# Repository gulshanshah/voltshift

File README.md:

# VoltShift

**Automatic voltage-stable line switcher.**

In many villages and homes the supply arrives unbalanced — some lines sit weak,
some sit high, and people walk over to the board and move the home supply to the
line that behaves. VoltShift does that switching automatically: it watches three
incoming lines, picks the one that is stable near 240 V, and drives a selector
switch onto it with a stepper motor — or to OFF when no line is safe.

## Repository layout

| Path | What it is |
| --- | --- |
| `pcb/` | KiCad 9 project — `voltshift.kicad_pro`, schematic, board and netlist |
| `firmware/` | ATmega328P firmware (bare-metal C, PlatformIO) |
| `media/` | Board renders, layer plots, schematic SVG and PDF |
| `docs/` | Schematic PDF and the ERC report |

## How it works

1. **Sensing** — three identical channels (R, Y, B), each a fusible 4R7 input
   resistor, three 150k 1 % series resistors stepping the AC line down, and a
   1N4007 rectifier turning it into a DC level the MCU can read. A 4k7 shunt,
   a 5.6 V zener and a 47 µF cap clamp and smooth that level.
2. **Isolation** — each channel feeds a PC817 optocoupler, so the mains domain
   stays galvanically separate from the logic domain; the opto output lands on
   an ATmega328P ADC input through a 10k pull-down.
3. **Decision** — the MCU samples all three inputs continuously, accepts only a
   line that reads stable near 240 V, and rejects anything too high or too low.
4. **Switching** — a 28BYJ-48 stepper driven by a ULN2003A turns the selector
   through four 45° positions: the healthy line, or OFF when nothing is in
   range.

The board keeps manual switching out of the equation — the home supply always
lands on the healthiest voltage.

## Hardware

- **MCU** — ATmega328P-PU @ 16 MHz, with ISP (2×3) and 5 V TTL UART headers
- **Drive** — ULN2003A → 28BYJ-48 stepper selector
- **Sensing** — 3× opto-isolated AC channels → ADC0/1/2
- **Power** — external 5 V DC input, ferrite-isolated AVCC
- **Board** — 170 × 100 mm, 2-layer, mains domain and logic domain split with
  ≥ 6 mm creepage between them and a ground pour kept to the logic side only
- **Status** — schematic and routed PCB complete, ERC clean (0 errors,
  0 warnings)

### Safety

This board handles **240 VAC mains**. Sense resistors must be rated for the
working voltage, creepage/clearance must be respected, and the board must not
be touched while powered. It is a prototype — validate it against your local
electrical rules before putting it anywhere near a real installation.

## Media

| Top | Bottom |
| --- | --- |
|  |  |

- [Schematic (SVG)](media/voltshift.svg) · [Schematic (PDF)](media/voltshift-schematic.pdf)
- [Top copper layout](media/voltshift-layout-top.svg) · [Bottom copper layout](media/voltshift-layout-bottom.svg)

## Firmware

The firmware lives in `firmware/` and runs directly on the ATmega328P — no Arduino framework, no communication, fully automatic, about 1.8 KB of flash.

```
firmware/include/config.h   # thresholds, calibration, pin map, timing
firmware/src/adc.c           # averaged ADC reads + counts-to-decivolts calibration
firmware/src/selector.c      # line validity, best-line choice, hysteresis
firmware/src/stepper.c       # half-step driver for the 28BYJ-48 selector
firmware/src/led.c           # status LED patterns
firmware/src/main.c          # 1 ms tick, sample/evaluate loop, watchdog
```

Every 10 ms each channel is averaged and converted to decivolts; every 100 ms a line is accepted only if it sits inside 205.0–255.0 V with under 2.0 V of ripple. The selector moves to the accepted line closest to 240 V, only after that line beats the held one by more than 3 V for four consecutive evaluations, and drops to OFF the moment the held line goes invalid. The status LED reports state: slow blink while starting up, solid on a line, fast blink on OFF or while the motor is moving.

Build and flash with PlatformIO:

```
cd firmware
pio run                     # builds firmware.elf / firmware.hex
pio run -t upload           # default programmer is usbasp (ISP)
```

Calibration is per-channel in `include/config.h` — `VS_CAL_OFFSET_*` and `VS_CAL_SPAN_*_PER_100V` map raw ADC counts to voltage; tune them against a known-good meter before trusting the decisions.

## Working on the design

Open `pcb/voltshift.kicad_pro` in KiCad 9 and edit the schematic and the board
directly. Run the Electrical Rules Checker after any change — the last check
came back clean (0 errors, 0 warnings).

Keep the two domains apart while editing: mains circuitry stays left of the
isolation gap, the ground pour belongs to the logic side only, and the 6 mm
creepage between them must survive any move. The exported schematic PDF and
the ERC report are in `docs/`.

## Status

Schematic and PCB are done and ERC-clean, and the firmware builds for the
ATmega328P. Next up: fab the board and build the first unit.

## License

MIT — see [LICENSE](LICENSE).

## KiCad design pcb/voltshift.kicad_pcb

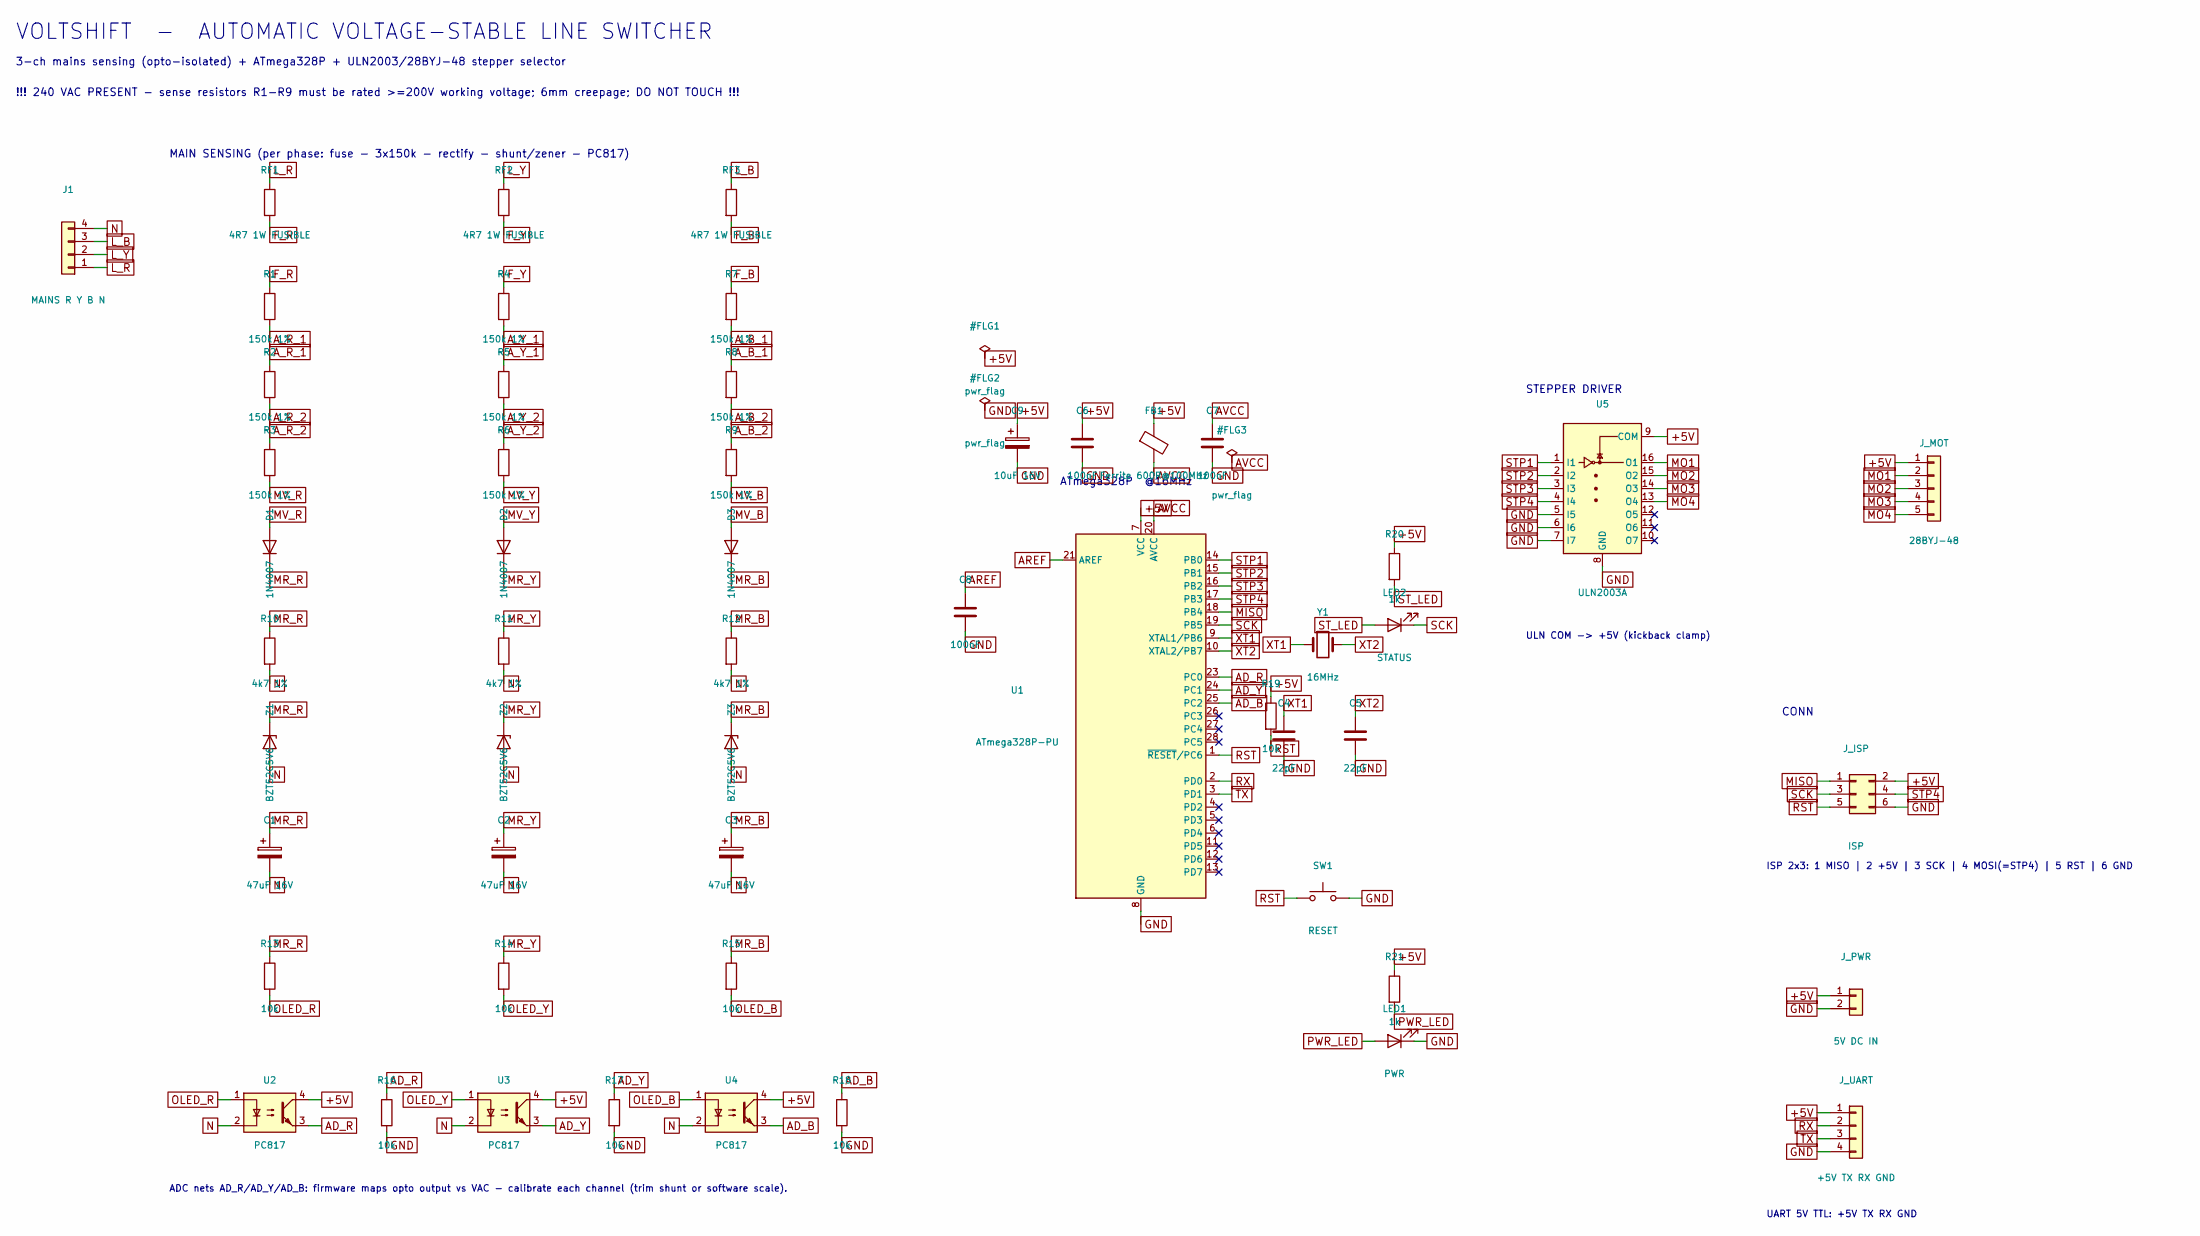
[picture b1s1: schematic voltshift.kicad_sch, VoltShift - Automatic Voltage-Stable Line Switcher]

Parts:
C1, C2, C3: 47uF 16V; CP_Radial_D5.0mm_P2.50mm
C4, C5: 22pF; C_0805_2012Metric
C6, C7, C8: 100nF; C_0805_2012Metric
C9: 10uF 16V; CP_Radial_D5.0mm_P2.50mm
D1, D2, D3: 1N4007; D_DO-41_SOD81_P10.16mm_Horizontal
FB1: Ferrite 600R@100MHz; L_0805_2012Metric
J1: MAINS R Y B N; TerminalBlock_bornier-4_P5.08mm
J_ISP: ISP; IDC-Header_2x03_P2.54mm_Vertical
J_MOT: 28BYJ-48; PinHeader_1x05_P2.54mm_Vertical
J_PWR: 5V DC IN; TerminalBlock_bornier-2_P5.08mm
J_UART: +5V TX RX GND; PinHeader_1x04_P2.54mm_Vertical
LED1: PWR; LED_0805_2012Metric
LED2: STATUS; LED_0805_2012Metric
R1, R2, R3, R4, R5, R6, R7, R8, R9: 150k 1%; R_1206_3216Metric
R10, R11, R12: 4k7 1%; R_0805_2012Metric
R13, R14, R15, R16, R17, R18, R19: 10k; R_0805_2012Metric
R20, R21: 1k; R_0805_2012Metric
RF1, RF2, RF3: 4R7 1W FUSIBLE; R_Axial_DIN0207_L6.3mm_D2.5mm_P10.16mm_Horizontal
SW1: RESET; SW_PUSH_6mm
U1: ATmega328P-PU; DIP-28_W15.24mm
U2, U3, U4: PC817; DIP-4_W7.62mm
U5: ULN2003A; DIP-16_W7.62mm
Y1: 16MHz; Crystal_HC49-4H_Vertical
Z1, Z2, Z3: BZT52C5V6; D_SOD-123

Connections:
+5V: C6.1, C9.1, FB1.1, J_ISP.2, J_MOT.1, J_PWR.1, J_UART.1, R19.1, R20.1, R21.1, U1.7 (VCC), U2.4, U3.4, U4.4, U5.9 (COM)
AD_B: R18.1, U1.25 (PC2), U4.3
AD_R: R16.1, U1.23 (PC0), U2.3
AD_Y: R17.1, U1.24 (PC1), U3.3
AREF: C8.1, U1.21 (AREF)
AVCC: C7.1, FB1.2, U1.20 (AVCC)
A_B_1: R7.2, R8.1
A_B_2: R8.2, R9.1
A_R_1: R1.2, R2.1
A_R_2: R2.2, R3.1
A_Y_1: R4.2, R5.1
A_Y_2: R5.2, R6.1
F_B: R7.1, RF3.2
F_R: R1.1, RF1.2
F_Y: R4.1, RF2.2
GND: C4.2, C5.2, C6.2, C7.2, C8.2, C9.2, J_ISP.6, J_PWR.2, J_UART.4, LED1.1 (K), R16.2, R17.2, R18.2, SW1.2, U1.8 (GND), U1.22 (GND), U5.5 (I5), U5.6 (I6), U5.7 (I7), U5.8 (GND)
L_B: J1.3, RF3.1
L_R: J1.1, RF1.1
L_Y: J1.2, RF2.1
MISO: J_ISP.1, U1.18 (PB4)
MO1: J_MOT.2, U5.16 (O1)
MO2: J_MOT.3, U5.15 (O2)
MO3: J_MOT.4, U5.14 (O3)
MO4: J_MOT.5, U5.13 (O4)
MR_B: C3.1, D3.1 (K), R12.1, R15.1, Z3.1 (K)
MR_R: C1.1, D1.1 (K), R10.1, R13.1, Z1.1 (K)
MR_Y: C2.1, D2.1 (K), R11.1, R14.1, Z2.1 (K)
MV_B: D3.2 (A), R9.2
MV_R: D1.2 (A), R3.2
MV_Y: D2.2 (A), R6.2
N: C1.2, C2.2, C3.2, J1.4, R10.2, R11.2, R12.2, U2.2, U3.2, U4.2, Z1.2 (A), Z2.2 (A), Z3.2 (A)
OLED_B: R15.2, U4.1
OLED_R: R13.2, U2.1
OLED_Y: R14.2, U3.1
PWR_LED: LED1.2 (A), R21.2
RST: J_ISP.5, R19.2, SW1.1, U1.1 (~RESET/PC6)
RX: J_UART.2, U1.2 (PD0)
SCK: J_ISP.3, LED2.1 (K), U1.19 (PB5)
STP1: U1.14 (PB0), U5.1 (I1)
STP2: U1.15 (PB1), U5.2 (I2)
STP3: U1.16 (PB2), U5.3 (I3)
STP4: J_ISP.4, U1.17 (PB3), U5.4 (I4)
ST_LED: LED2.2 (A), R20.2
TX: J_UART.3, U1.3 (PD1)
XT1: C4.1, U1.9 (XTAL1/PB6), Y1.1
XT2: C5.1, U1.10 (XTAL2/PB7), Y1.2

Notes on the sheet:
VOLTSHIFT - AUTOMATIC VOLTAGE-STABLE LINE SWITCHER
3-ch mains sensing (opto-isolated) + ATmega328P + ULN2003/28BYJ-48 stepper selector
!!! 240 VAC PRESENT - sense resistors R1-R9 must be rated >=200V working voltage; 6mm creepage; DO NOT TOUCH !!!
MAIN SENSING (per phase: fuse - 3x150k - rectify - shunt/zener - PC817)
ATmega328P @16MHz
STEPPER DRIVER
CONN
ADC nets AD_R/AD_Y/AD_B: firmware maps opto output vs VAC - calibrate each channel (trim shunt or software scale).
ISP 2x3: 1 MISO | 2 +5V | 3 SCK | 4 MOSI(=STP4) | 5 RST | 6 GND
UART 5V TTL: +5V TX RX GND
ULN COM -> +5V (kickback clamp)

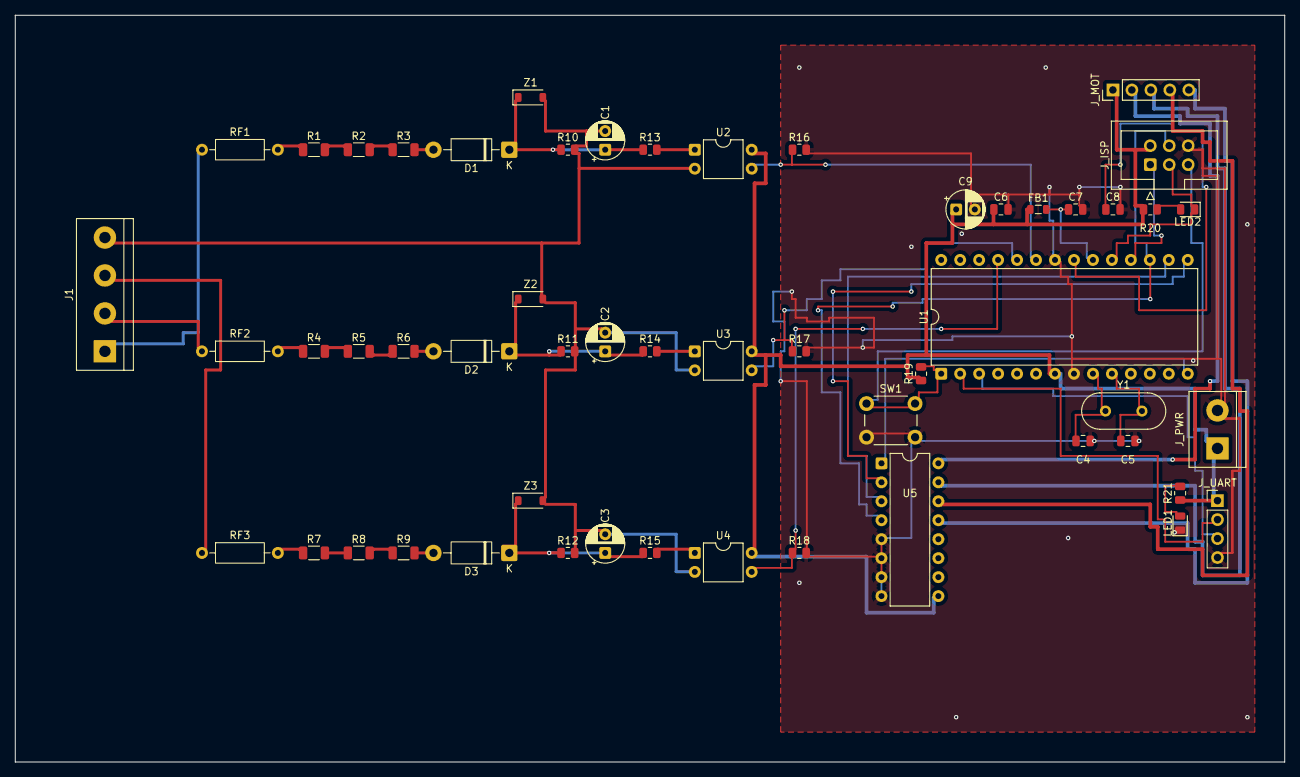
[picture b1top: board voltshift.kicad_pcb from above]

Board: 2 copper layers, 170.0 x 100.0 mm, 54 parts (0 on the bottom side), 46 nets.
